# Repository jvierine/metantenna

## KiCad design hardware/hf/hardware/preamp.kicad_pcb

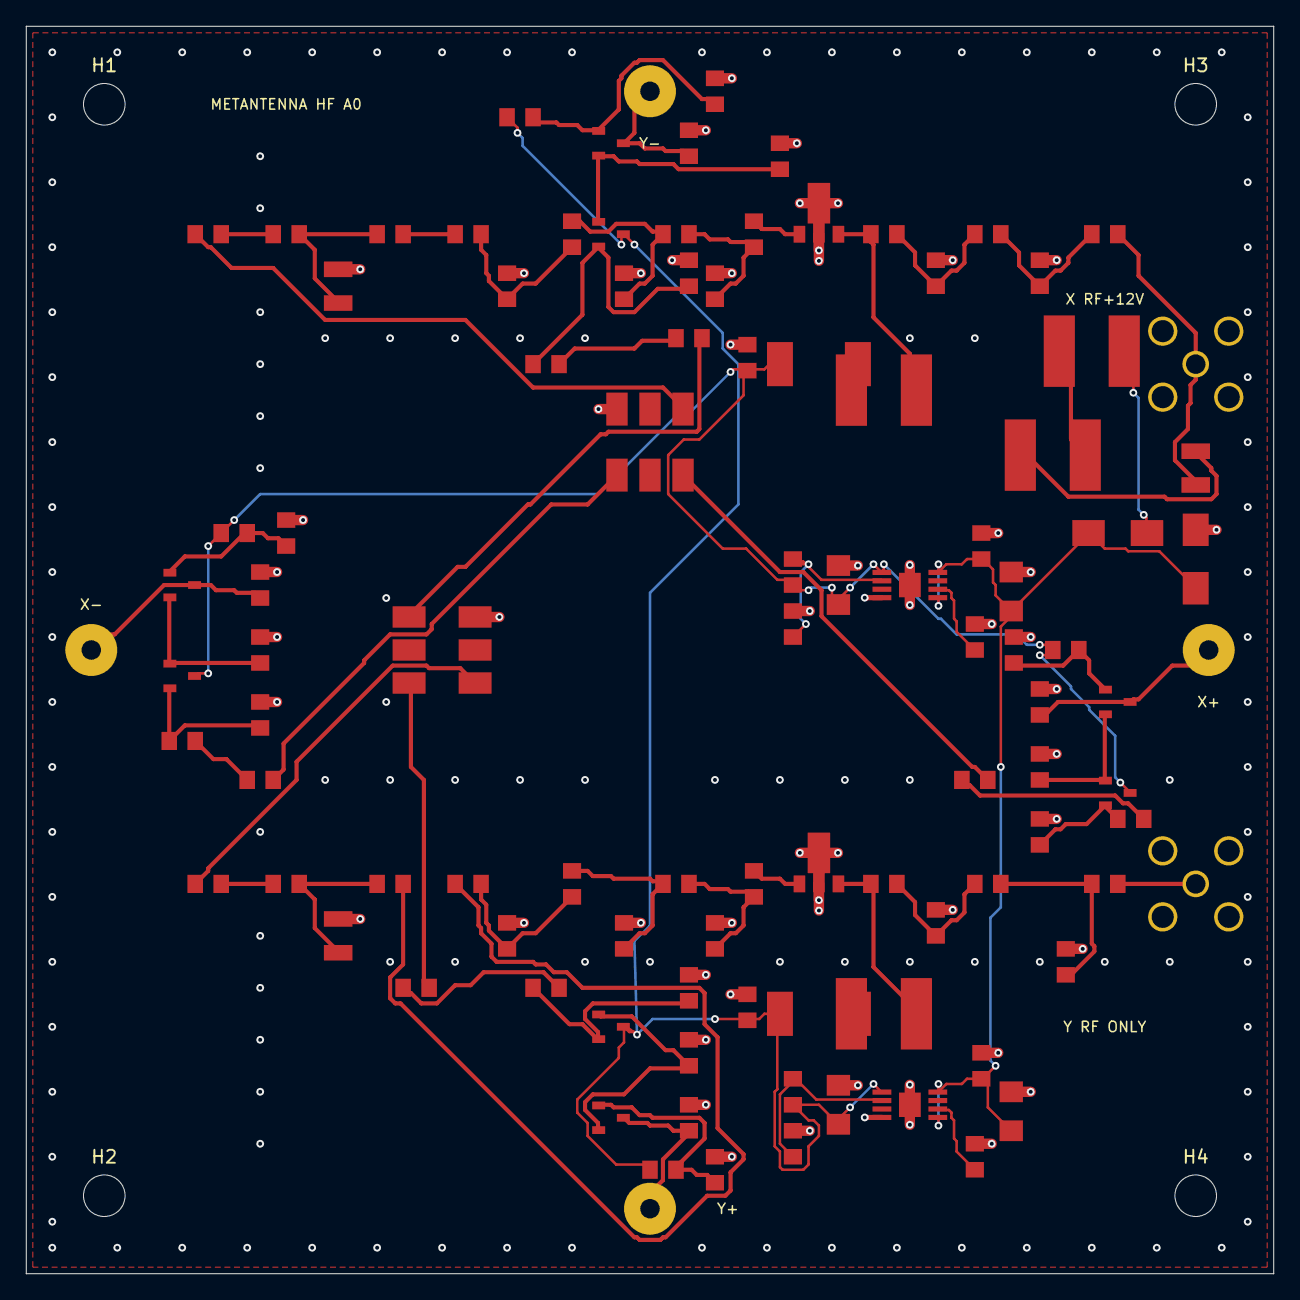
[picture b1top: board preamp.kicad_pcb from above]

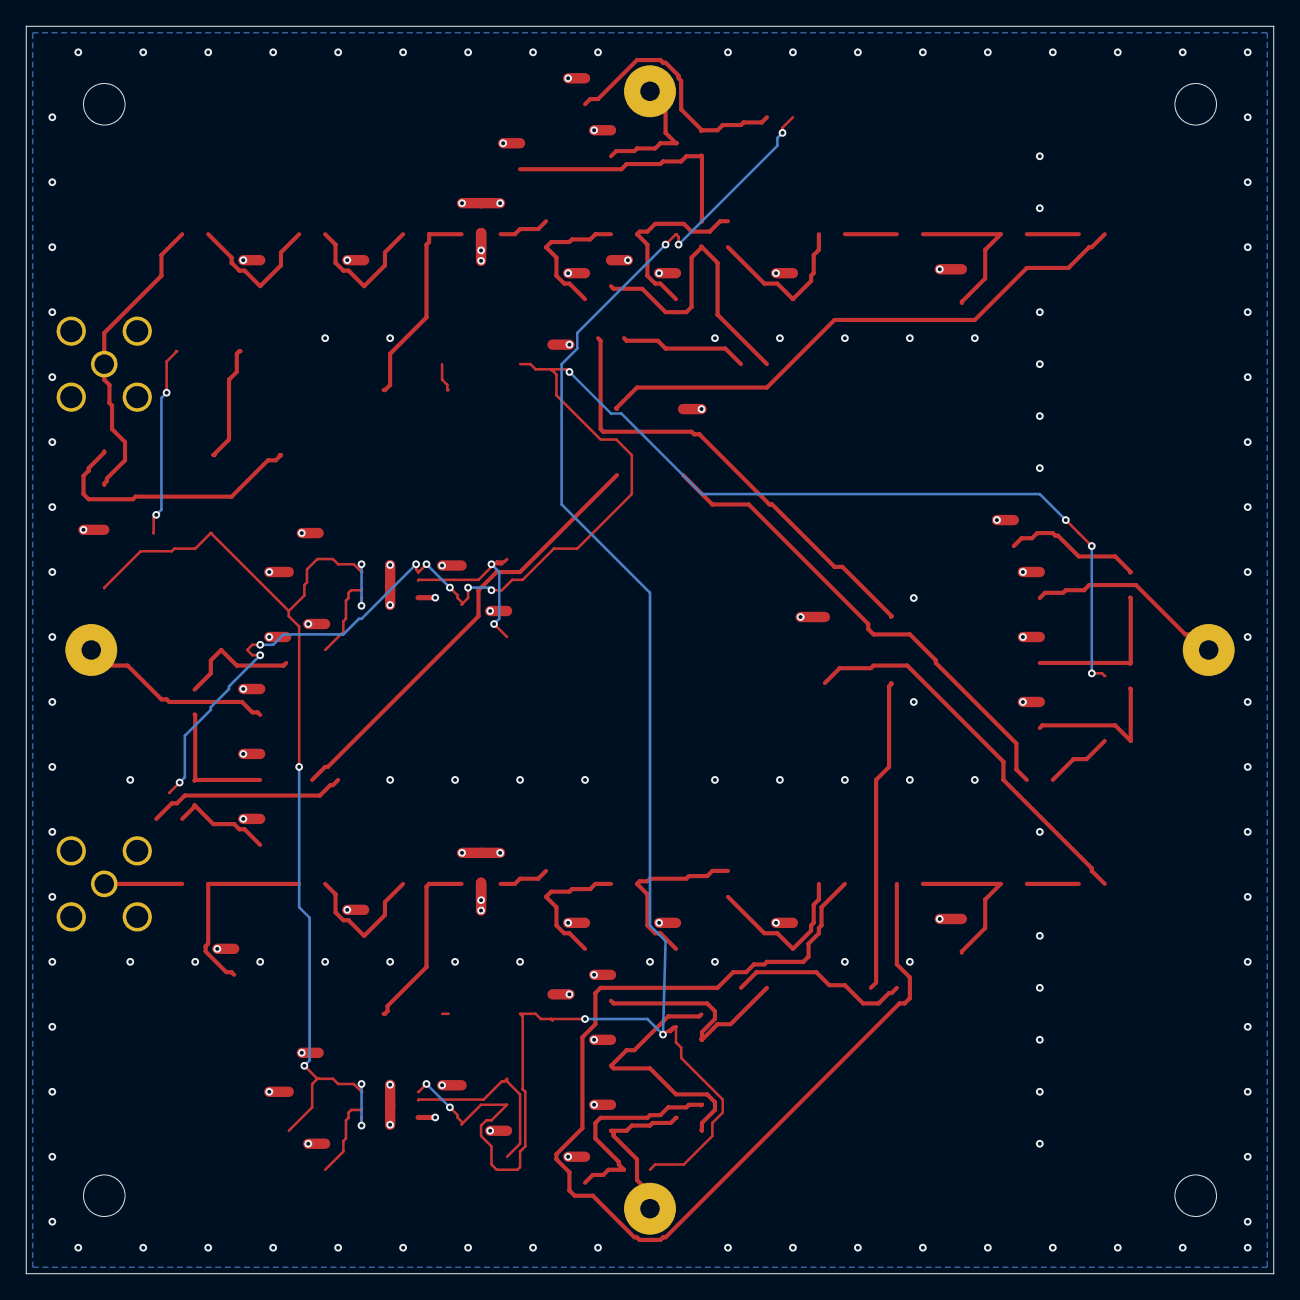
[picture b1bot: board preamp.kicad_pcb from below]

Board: 4 copper layers, 96.0 x 96.0 mm, 105 parts (2 on the bottom side), 61 nets.

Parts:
C108, C109, C130, C140, C208, C209, C230, C240: 220n 50V; 0805
C110, C112, C210, C212: 10u 25V; 1206
C111, C114, C211, C214: 100n 50V; 0805
C113, C213: 10n 50V; 0805
C131, C141, C231, C241: 100n; 0805
C160, C161, C260, C261: 33n; 0805
C162, C164, C262, C264: 130p; 0805
C163, C263: 220p; 0805
D103: SS14; SMA_DIODE
D104: SMAJ15A; SMA_DIODE
H1, H2, H3, H4: MountingHole
J101: X dipole; ANT_M3
J102: X RF +12V; SMA
J201: Y dipole; ANT_M3
J202: Y RF, DC blocked; SMA
L104: 1u; 1008
L105, L106, L107, L205: 100u; SRN6045
L160, L260: 39u; 1008
L161, L164, L261, L264: 120n; 0805
L162, L163, L262, L263: 470n; 0805
Q130, Q140, Q230, Q240: MMBFJ310LT1G; SOT23
Q131, Q141, Q231, Q241: BC850C,235; SOT23
R103, R105, R203, R205: 294; 0805
R104, R204: 18; 0805
R106, R206: 40.2k; 0805
R107, R207: 10k; 0805
R108, R208: 15 1W; 2512
R130, R140, R230, R240: 1M; 0805
R131, R141, R231, R241: 180; 0805
R132, R142, R232, R242: 220; 0805
R133, R143, R233, R243: 2.2; 0805
R134, R144, R234, R244: 10; 0805
R160, R260: 39; 0805
T101, T201: ADT1-6T+; CD542
U101, U201: GALI-74+; SOT89
U102, U202: TPS7A4901DGNR; MSOP8EP

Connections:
/GND: C110.2, C111.2, C112.2, C113.2, C114.2, C131.2, C141.2, C162.2, C163.2, C164.2, C210.2, C211.2, C212.2, C213.2, C214.2, C231.2, C241.2, C262.2, C263.2, C264.2, D104.2, J102.2, J202.2, L160.2, L260.2, R103.2, R105.2, R107.2, R130.2, R131.2, R132.2, R140.2, R141.2, R142.2, R203.2, R205.2, R207.2, R230.2, R231.2, R232.2, R240.2, R241.2, R242.2, T101.6, T201.6, U101.2, U102.4, U102.9, U201.2, U202.4, U202.9
/HF_PWR1: L104.2, L106.1
/HF_PWR2: L106.2, L107.1
/V12: C110.1, C111.1, C210.1, C211.1, D103.1, D104.1, U102.5, U102.8, U202.5, U202.8
/X_AC_N: C130.2, R133.1
/X_AC_P: C140.2, R143.1
/X_AMP_IN: L164.2, U101.1
/X_AMP_OUT: C108.1, L105.2, U101.3
/X_ANT_N: J101.1, Q130.3, R130.1
/X_ANT_P: J101.2, Q140.3, R140.1
/X_BAL_N: R133.2, T101.1
/X_BAL_P: R143.2, T101.3
/X_BIAS: L105.1, R108.2
/X_COAX: C109.2, J102.1, L104.1
/X_D_N: C131.1, Q130.1, R134.2
/X_D_P: C141.1, Q140.1, R144.2
/X_EF_N: C130.1, Q131.2, R132.1
/X_EF_P: C140.1, Q141.2, R142.1
/X_FB: R106.2, R107.1, U102.2
/X_HP0: C160.1, R160.2
/X_HP1: C160.2, C161.1, L160.1
/X_LP0: C161.2, L161.1
/X_LP1: C162.1, L161.2, L162.1
/X_LP2: C163.1, L162.2, L163.1
/X_LP3: C164.1, L163.2, L164.1
/X_NR: C113.1, U102.6
/X_PAD_IN: C108.2, R103.1, R104.1
/X_PAD_OUT: C109.1, R104.2, R105.1
/X_RAW: D103.2, L107.2
/X_RF_IN: R160.1, T101.4
/X_SF_N: Q130.2, Q131.1, R131.1
/X_SF_P: Q140.2, Q141.1, R141.1
/X_V8: C112.1, C114.1, Q131.3, Q141.3, R106.1, R108.1, R134.1, R144.1, U102.1
/Y_AC_N: C230.2, R233.1
/Y_AC_P: C240.2, R243.1
/Y_AMP_IN: L264.2, U201.1
/Y_AMP_OUT: C208.1, L205.2, U201.3
/Y_ANT_N: J201.1, Q230.3, R230.1
/Y_ANT_P: J201.2, Q240.3, R240.1
/Y_BAL_N: R233.2, T201.1
/Y_BAL_P: R243.2, T201.3
/Y_BIAS: L205.1, R208.2
/Y_COAX: C209.2, J202.1
/Y_D_N: C231.1, Q230.1, R234.2
/Y_D_P: C241.1, Q240.1, R244.2
/Y_EF_N: C230.1, Q231.2, R232.1
/Y_EF_P: C240.1, Q241.2, R242.1
/Y_FB: R206.2, R207.1, U202.2
/Y_HP0: C260.1, R260.2
/Y_HP1: C260.2, C261.1, L260.1
/Y_LP0: C261.2, L261.1
/Y_LP1: C262.1, L261.2, L262.1
/Y_LP2: C263.1, L262.2, L263.1
/Y_LP3: C264.1, L263.2, L264.1
/Y_NR: C213.1, U202.6
/Y_PAD_IN: C208.2, R203.1, R204.1
/Y_PAD_OUT: C209.1, R204.2, R205.1
/Y_RF_IN: R260.1, T201.4
/Y_SF_N: Q230.2, Q231.1, R231.1
/Y_SF_P: Q240.2, Q241.1, R241.1
/Y_V8: C212.1, C214.1, Q231.3, Q241.3, R206.1, R208.1, R234.1, R244.1, U202.1

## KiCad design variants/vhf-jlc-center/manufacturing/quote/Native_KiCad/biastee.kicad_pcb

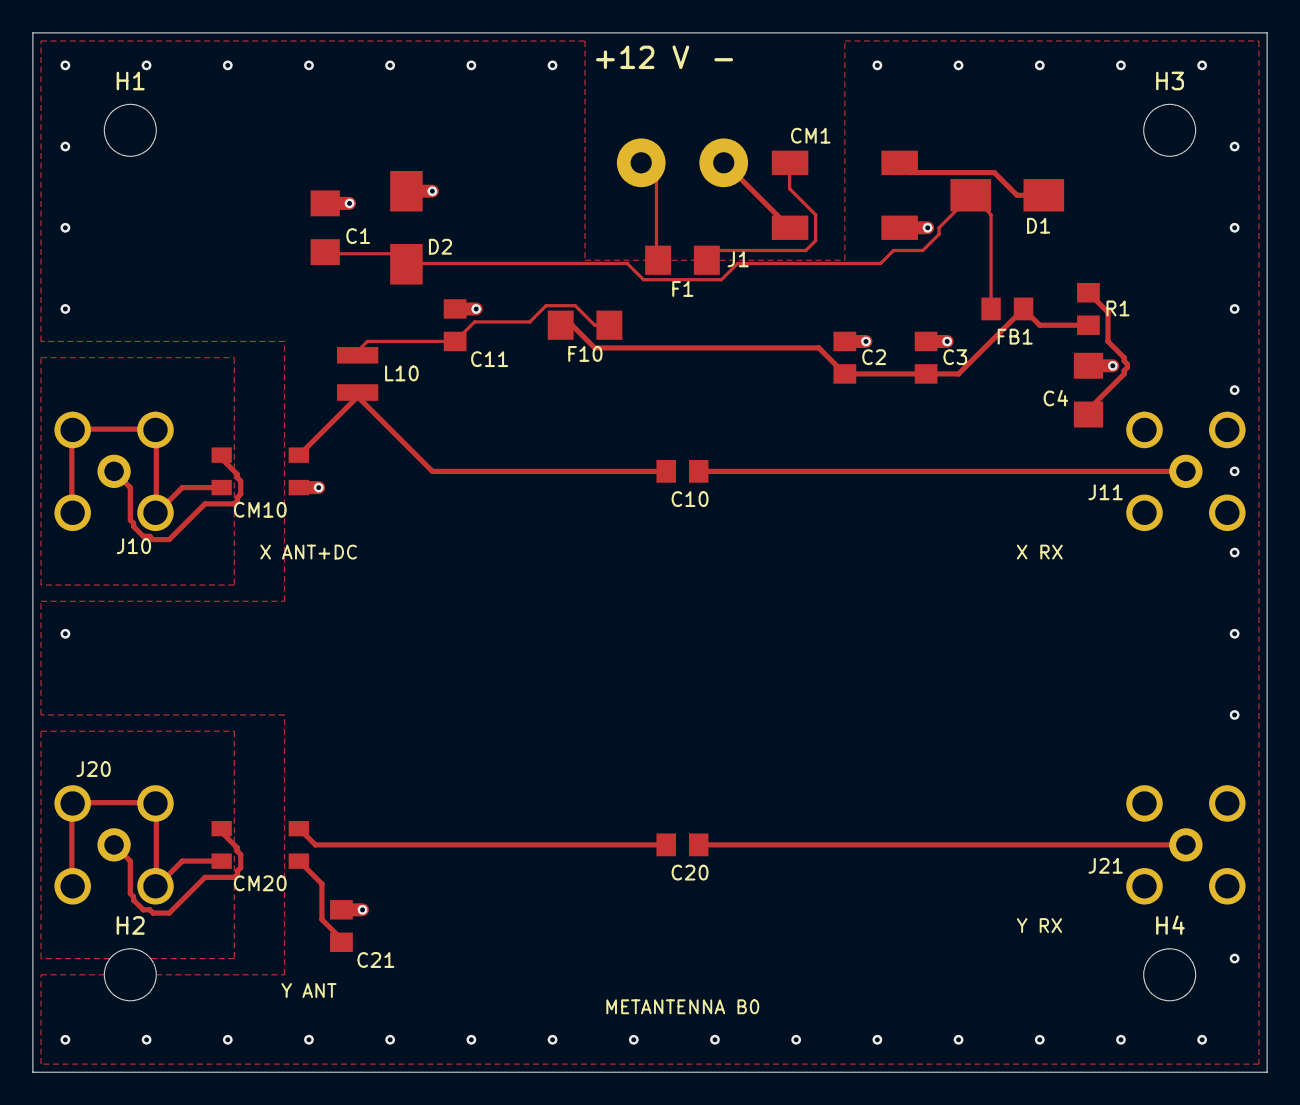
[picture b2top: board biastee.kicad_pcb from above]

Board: 4 copper layers, 76.0 x 64.0 mm, 27 parts (0 on the bottom side), 18 nets.

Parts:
C1, C4: 10u 25V; 1206
C2, C10, C20, C21: 1n; 0805
C3, C11: 100n 50V; 0805
CM1: 700R CM @100MHz; ACM7060
CM10, CM20: 900R CM @100MHz; ACM4520
D1: SS14; SMA_DIODE
D2: SMAJ15A; SMA_DIODE
F1, F10: 500mA PTC; 1206
FB1: 600R @100MHz; 0805
H1, H2, H3, H4: MountingHole
J1: 12 V input; TERM2
J10: X ANT +DC; SMA_RA
J11: X RX DC BLOCK; SMA_RA
J20: Y ANT RF only; SMA_RA
J21: Y RX DC BLOCK; SMA_RA
L10: 1u; APV2520
R1: 1R; 0805

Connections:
/CM_POS: CM1.4, D1.2
/DAMP: C4.1, R1.2
/FILTERED: C2.1, C3.1, F10.1, FB1.2, R1.1
/GND: C1.2, C2.2, C3.2, C4.2, C11.2, C21.2, CM1.3, CM10.3, D2.2, J11.2, J21.2
/PROTECTED: C1.1, D1.1, D2.1, FB1.1
/SUPPLY_RETURN: CM1.2, J1.2
/VIN: F1.1, J1.1
/VIN_FUSED: CM1.1, F1.2
/X_ANT_CENTER: CM10.1, J10.1
/X_ANT_RETURN: CM10.2, J10.2
/X_COAX: C10.1, CM10.4, L10.1
/X_DC: C11.1, F10.2, L10.2
/X_RX: C10.2, J11.1
/Y_ANT_CENTER: CM20.1, J20.1
/Y_ANT_RETURN: CM20.2, J20.2
/Y_COAX: C20.1, CM20.4
/Y_RETURN_BLOCKED: C21.1, CM20.3
/Y_RX: C20.2, J21.1

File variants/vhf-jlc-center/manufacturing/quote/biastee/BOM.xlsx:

Comment | Designator | Footprint | Manufacturer Part Number | LCSC Part Number | Quantity per board
100n 50V | C3,C11 | 0805 | GRM21BR71H104KA01L | SOURCE BY EXACT MPN | 2
10u 25V | C4,C1 | 1206 | GRM31CR61E106KA12L | C77090 | 2
12 V input | J1 | TERM2 | 1729128 | C7509570 | 1
1R | R1 | 0805 | 0805W8F100KT5E | C25271 | 1
1n | C2,C10,C20,C21 | 0805 | CGA4F3C0G2E102JT0Y0N | C338119 | 4
1u | L10 | APV2520 | AHW2520C-1R0JTF | C6364738 | 1
500mA PTC | F1,F10 | 1206 | 1206L050/24YR | SOURCE BY EXACT MPN | 2
600R @100MHz | FB1 | 0805 | BLM21PG601SN1D | C41556732 | 1
700R CM @100MHz | CM1 | ACM7060 | ACM7060-701-2PL-TL01 | C78246 | 1
900R CM @100MHz | CM10,CM20 | ACM4520 | ACM4520-901-2P-T000 | C41519 | 2
SMAJ15A | D2 | SMA_DIODE | SMAJ15A | SOURCE BY EXACT MPN | 1
SS14 | D1 | SMA_DIODE | SS14 | SOURCE BY EXACT MPN | 1
X ANT +DC | J10 | SMA_RA | SMA-KWE-323C-H13X23-LW | C5723201 | 1
X RX DC BLOCK | J11 | SMA_RA | SMA-KWE-323C-H13X23-LW | C5723201 | 1
Y ANT RF only | J20 | SMA_RA | SMA-KWE-323C-H13X23-LW | C5723201 | 1
Y RX DC BLOCK | J21 | SMA_RA | SMA-KWE-323C-H13X23-LW | C5723201 | 1
